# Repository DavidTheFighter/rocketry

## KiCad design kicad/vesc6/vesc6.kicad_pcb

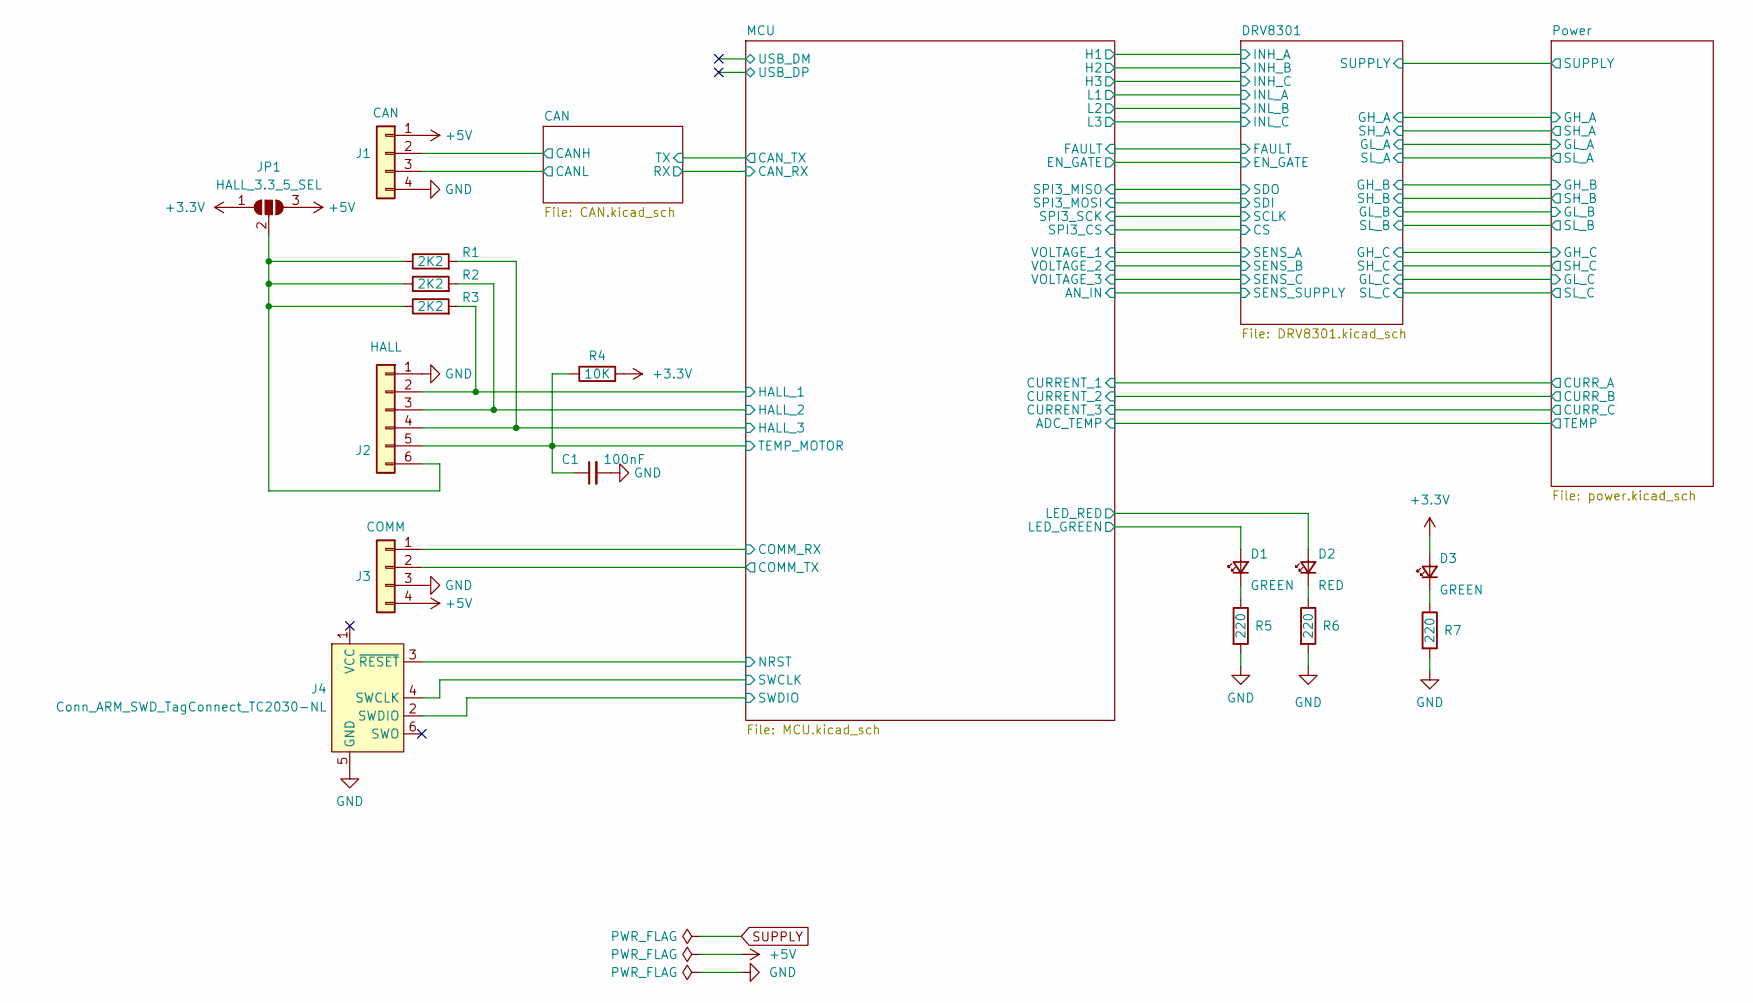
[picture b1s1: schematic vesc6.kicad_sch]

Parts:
C1: 100nF; C_0402_1005Metric; LCSC C307331
D1, D3: GREEN; C_0603_1608Metric; LCSC C72043
D2: RED; C_0603_1608Metric; LCSC C2286
J1: CAN; JST_PH_B4B-PH-K_1x04_P2.00mm_Vertical
J2: HALL; JST_PH_B6B-PH-K_1x06_P2.00mm_Vertical
J3: COMM; JST_PH_B4B-PH-K_1x04_P2.00mm_Vertical
J4: Conn_ARM_SWD_TagConnect_TC2030-NL; Tag-Connect_TC2030-IDC-NL_2x03_P1.27mm_Vertical
JP1: HALL_3.3_5_SEL; SolderJumper-3_P2.0mm_Open_TrianglePad1.0x1.5mm
R1, R2, R3: 2K2; C_0402_1005Metric; LCSC C25879
R4: 10K; R_0402_1005Metric; LCSC C25744
R5, R6, R7: 220; R_0402_1005Metric; LCSC C25091

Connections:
+3.3V: D3.2 (A), JP1.1 (A), R4.2; also elsewhere on the board
+5V: J1.1, J3.4, JP1.3 (B); also elsewhere on the board
/CAN/CANH: J1.2; also elsewhere on the board
/CAN/CANL: J1.3; also elsewhere on the board
/MCU/COMM_RX: J3.1; also elsewhere on the board
/MCU/COMM_TX: J3.2; also elsewhere on the board
/MCU/HALL_1: J2.2, R3.2; also elsewhere on the board
/MCU/HALL_2: J2.3, R2.2; also elsewhere on the board
/MCU/HALL_3: J2.4, R1.2; also elsewhere on the board
/MCU/LED_GREEN: D1.2 (A); also elsewhere on the board
/MCU/LED_RED: D2.2 (A); also elsewhere on the board
/MCU/NRST: J4.3 (~RESET); also elsewhere on the board
/MCU/SWCLK: J4.4 (SWCLK); also elsewhere on the board
/MCU/SWDIO: J4.2 (SWDIO); also elsewhere on the board
/MCU/TEMP_MOTOR: C1.1, J2.5, R4.1; also elsewhere on the board
GND: C1.2, J1.4, J2.1, J3.3, J4.5 (GND), R5.2, R6.2, R7.2; also elsewhere on the board
unnamed: D1.1 (K), R5.1
unnamed: D2.1 (K), R6.1
unnamed: D3.1 (K), R7.1
unnamed: J2.6, JP1.2 (C), R1.1, R2.1, R3.1

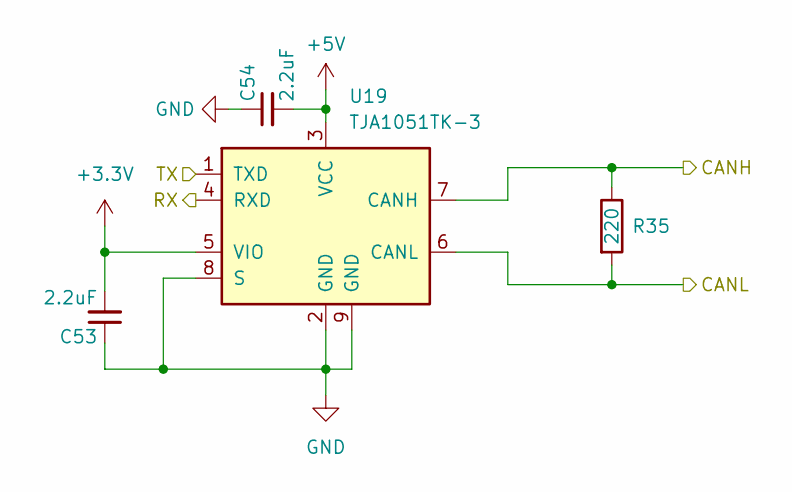
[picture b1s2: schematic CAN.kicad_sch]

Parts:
C53, C54: 2.2uF; R_0603_1608Metric; LCSC C23630
R35: 220; R_0402_1005Metric; LCSC C25091
U19: TJA1051TK-3; DFN-8-1EP_3x3mm_P0.65mm_EP1.55x2.4mm; LCSC C124020

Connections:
+3.3V: C53.2, U19.5 (VIO); also elsewhere on the board
+5V: C54.2, U19.3 (VCC); also elsewhere on the board
/CAN/CANH: R35.1, U19.7 (CANH); also elsewhere on the board
/CAN/CANL: R35.2, U19.6 (CANL); also elsewhere on the board
/CAN/RX: U19.4 (RXD); also elsewhere on the board
/CAN/TX: U19.1 (TXD); also elsewhere on the board
GND: C53.1, C54.1, U19.2 (GND), U19.8 (S), U19.9 (GND); also elsewhere on the board

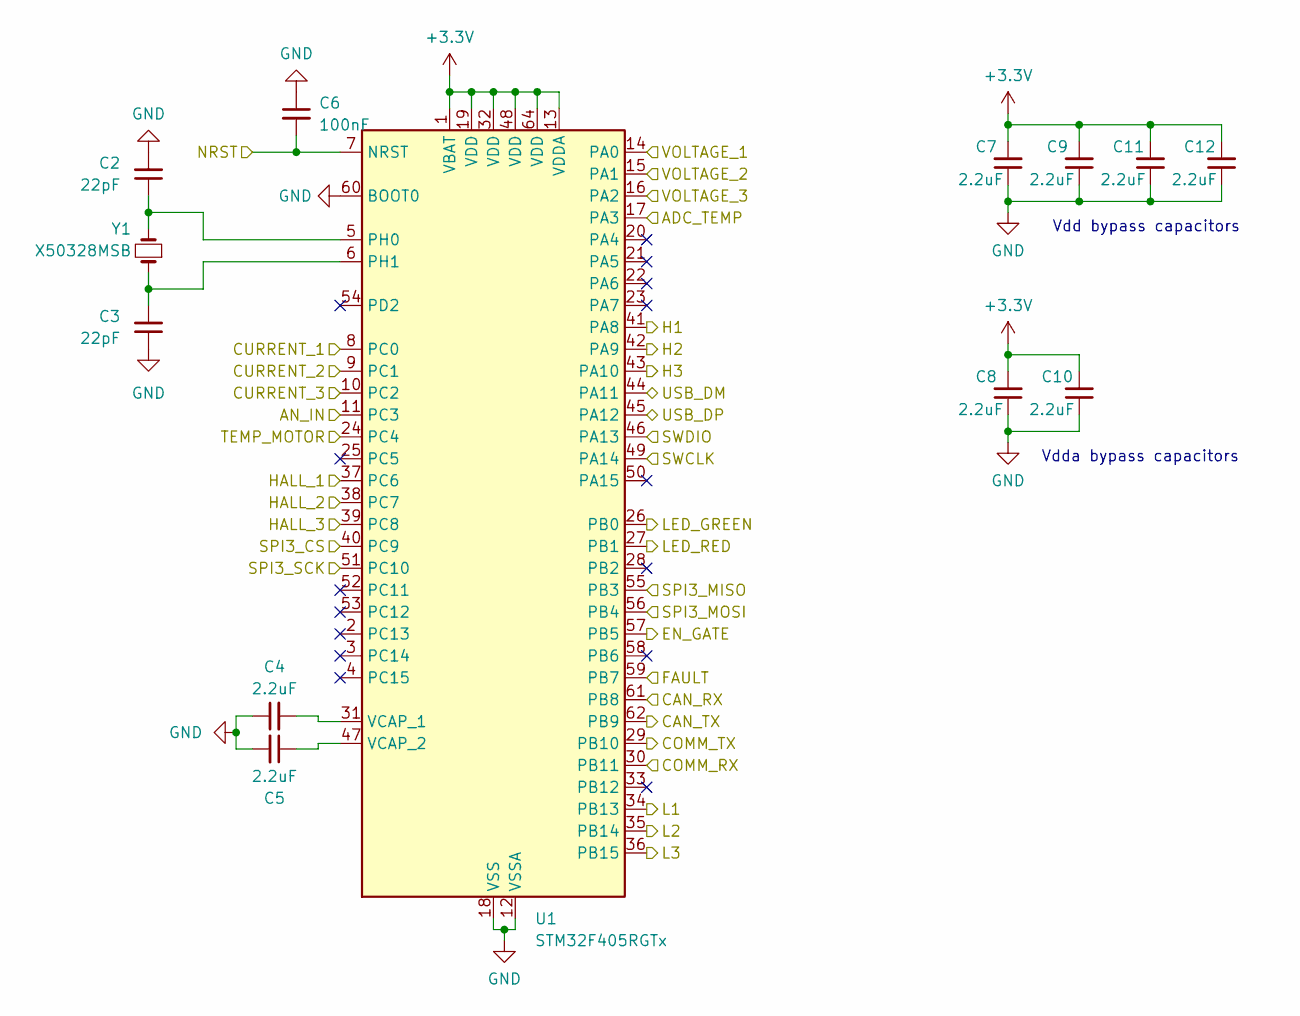
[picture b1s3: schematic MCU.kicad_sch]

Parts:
C2, C3: 22pF; C_0402_1005Metric; LCSC C1555
C4, C5, C7, C8, C9, C10, C11, C12: 2.2uF; C_0603_1608Metric; LCSC C23630
C6: 100nF; C_0504_1310Metric; LCSC C307331
U1: STM32F405RGTx; LQFP-64_10x10mm_P0.5mm; LCSC C15742
Y1: X50328MSB; Crystal_SMD_5032-2Pin_5.0x3.2mm; LCSC C115962

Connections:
+3.3V: C7.2, C8.2, C9.2, C10.2, C11.2, C12.2, U1.1 (VBAT), U1.13 (VDDA), U1.19 (VDD), U1.32 (VDD), U1.48 (VDD), U1.64 (VDD); also elsewhere on the board
/CAN/RX: U1.61 (PB8); also elsewhere on the board
/CAN/TX: U1.62 (PB9); also elsewhere on the board
/DRV8301/CS: U1.40 (PC9); also elsewhere on the board
/DRV8301/EN_GATE: U1.57 (PB5); also elsewhere on the board
/DRV8301/FAULT: U1.59 (PB7); also elsewhere on the board
/DRV8301/INH_A: U1.41 (PA8); also elsewhere on the board
/DRV8301/INH_B: U1.42 (PA9); also elsewhere on the board
/DRV8301/INH_C: U1.43 (PA10); also elsewhere on the board
/DRV8301/INL_A: U1.34 (PB13); also elsewhere on the board
/DRV8301/INL_B: U1.35 (PB14); also elsewhere on the board
/DRV8301/INL_C: U1.36 (PB15); also elsewhere on the board
/DRV8301/SCLK: U1.51 (PC10); also elsewhere on the board
/DRV8301/SDI: U1.56 (PB4); also elsewhere on the board
/DRV8301/SDO: U1.55 (PB3); also elsewhere on the board
/DRV8301/SENS_A: U1.14 (PA0); also elsewhere on the board
/DRV8301/SENS_B: U1.15 (PA1); also elsewhere on the board
/DRV8301/SENS_C: U1.16 (PA2); also elsewhere on the board
/DRV8301/SENS_SUPPLY: U1.11 (PC3); also elsewhere on the board
/MCU/ADC_TEMP: U1.17 (PA3); also elsewhere on the board
/MCU/COMM_RX: U1.30 (PB11); also elsewhere on the board
/MCU/COMM_TX: U1.29 (PB10); also elsewhere on the board
/MCU/CURRENT_1: U1.8 (PC0); also elsewhere on the board
/MCU/CURRENT_2: U1.9 (PC1); also elsewhere on the board
/MCU/CURRENT_3: U1.10 (PC2); also elsewhere on the board
/MCU/HALL_1: U1.37 (PC6); also elsewhere on the board
/MCU/HALL_2: U1.38 (PC7); also elsewhere on the board
/MCU/HALL_3: U1.39 (PC8); also elsewhere on the board
/MCU/LED_GREEN: U1.26 (PB0); also elsewhere on the board
/MCU/LED_RED: U1.27 (PB1); also elsewhere on the board
/MCU/NRST: C6.2, U1.7 (NRST); also elsewhere on the board
/MCU/SWCLK: U1.49 (PA14); also elsewhere on the board
/MCU/SWDIO: U1.46 (PA13); also elsewhere on the board
/MCU/TEMP_MOTOR: U1.24 (PC4); also elsewhere on the board
/MCU/USB_DM: U1.44 (PA11)
/MCU/USB_DP: U1.45 (PA12)
GND: C2.2, C3.1, C4.1, C5.2, C6.1, C7.1, C8.1, C9.1, C10.1, C11.1, C12.1, U1.12 (VSSA), U1.18 (VSS), U1.60 (BOOT0), U1.63 (VSS); also elsewhere on the board
unnamed: C2.1, U1.5 (PH0), Y1.2
unnamed: C3.2, U1.6 (PH1), Y1.1
unnamed: C4.2, U1.31 (VCAP_1)
unnamed: C5.1, U1.47 (VCAP_2)

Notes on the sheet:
Vdda bypass capacitors
Vdd bypass capacitors

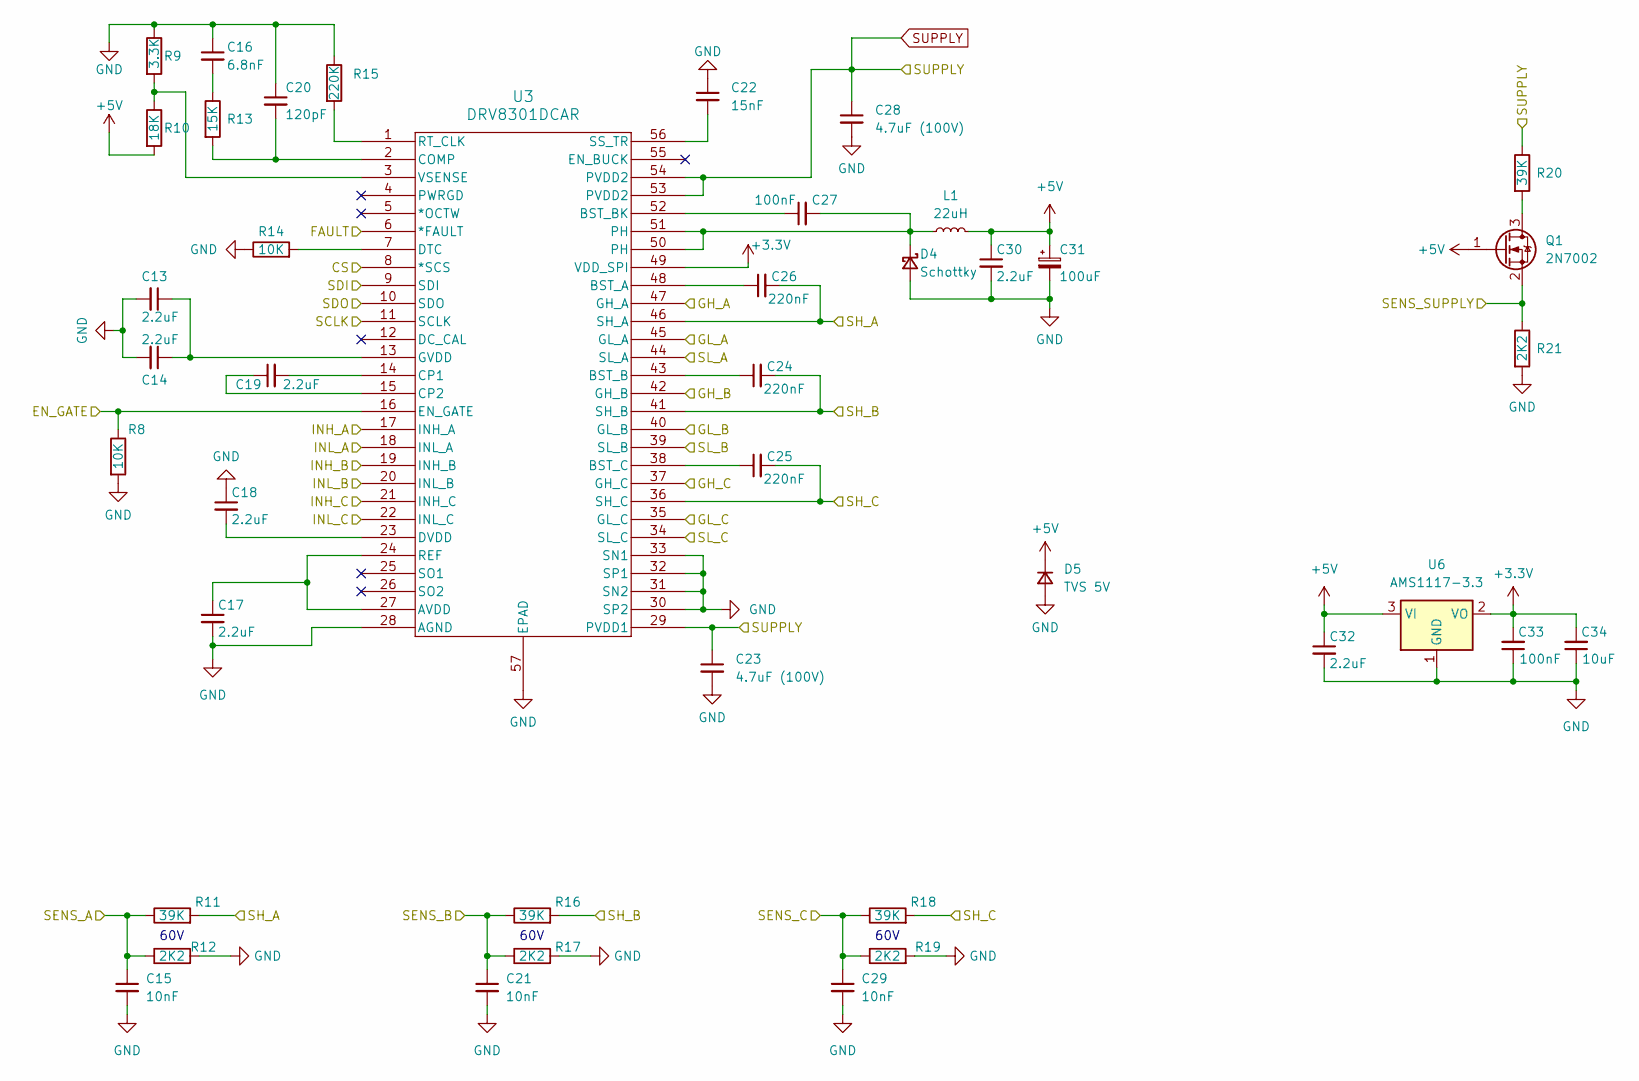
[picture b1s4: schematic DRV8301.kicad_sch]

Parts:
C13, C14, C17, C18, C19, C30, C32: 2.2uF; R_0603_1608Metric; LCSC C23630
C15, C21, C29: 10nF; C_0402_1005Metric; LCSC C15195
C16: 6.8nF; C_0603_1608Metric; LCSC C1631
C20: 120pF; C_0603_1608Metric; LCSC C599667
C22: 15nF; R_0402_1005Metric; LCSC C114405
C23, C28: 4.7uF (100V); R_1210_3225Metric; LCSC C2979983
C24, C25, C26: 220nF; R_0603_1608Metric; LCSC C21120
C27, C33: 100nF; C_0402_1005Metric; LCSC C307331
C31: 100uF; CP_Radial_D6.3mm_P2.50mm
C34: 10uF; C_0603_1608Metric; LCSC C96446
D4: Schottky; D_SMA; LCSC C8678
D5: TVS 5V; D_SOD-923; LCSC C96512
L1: 22uH; L_Bourns_SRP7028A_7.3x6.6mm; LCSC C497873
Q1: 2N7002; SOT-23; LCSC C8545
R8, R14: 10K; R_0402_1005Metric; LCSC C25744
R9: 3.3K; R_0402_1005Metric; LCSC C25890
R10: 18K; R_0603_1608Metric; LCSC C25810
R11, R16, R18, R20: 39K; C_0603_1608Metric; LCSC C23153
R12, R17, R19, R21: 2K2; C_0603_1608Metric; LCSC C4190
R13: 15K; R_0402_1005Metric; LCSC C25756
R15: 220K; R_0603_1608Metric; LCSC C22961
U3: DRV8301DCAR; HTSSOP-56-1EP_6.1x14mm_P0.5mm_EP3.61x6.35mm; LCSC C98969
U6: AMS1117-3.3; SOT-223-3_TabPin2; LCSC C6186

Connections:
+3.3V: C33.2, C34.2, U3.49 (VDD_SPI), U6.2 (VO); also elsewhere on the board
+5V: C30.1, C31.1, C32.1, D5.1 (K), L1.2, Q1.1 (G), R10.2, U6.3 (VI); also elsewhere on the board
/DRV8301/CS: U3.8 (*SCS); also elsewhere on the board
/DRV8301/EN_GATE: R8.1, U3.16 (EN_GATE); also elsewhere on the board
/DRV8301/FAULT: U3.6 (*FAULT); also elsewhere on the board
/DRV8301/GH_A: U3.47 (GH_A); also elsewhere on the board
/DRV8301/GH_B: U3.42 (GH_B); also elsewhere on the board
/DRV8301/GH_C: U3.37 (GH_C); also elsewhere on the board
/DRV8301/GL_A: U3.45 (GL_A); also elsewhere on the board
/DRV8301/GL_B: U3.40 (GL_B); also elsewhere on the board
/DRV8301/GL_C: U3.35 (GL_C); also elsewhere on the board
/DRV8301/INH_A: U3.17 (INH_A); also elsewhere on the board
/DRV8301/INH_B: U3.19 (INH_B); also elsewhere on the board
/DRV8301/INH_C: U3.21 (INH_C); also elsewhere on the board
/DRV8301/INL_A: U3.18 (INL_A); also elsewhere on the board
/DRV8301/INL_B: U3.20 (INL_B); also elsewhere on the board
/DRV8301/INL_C: U3.22 (INL_C); also elsewhere on the board
/DRV8301/SCLK: U3.11 (SCLK); also elsewhere on the board
/DRV8301/SDI: U3.9 (SDI); also elsewhere on the board
/DRV8301/SDO: U3.10 (SDO); also elsewhere on the board
/DRV8301/SENS_A: C15.1, R11.1, R12.1; also elsewhere on the board
/DRV8301/SENS_B: C21.1, R16.1, R17.1; also elsewhere on the board
/DRV8301/SENS_C: C29.1, R18.1, R19.1; also elsewhere on the board
/DRV8301/SENS_SUPPLY: Q1.2 (S), R21.1; also elsewhere on the board
/DRV8301/SH_A: C26.2, R11.2, U3.46 (SH_A); also elsewhere on the board
/DRV8301/SH_B: C24.2, R16.2, U3.41 (SH_B); also elsewhere on the board
/DRV8301/SH_C: C25.2, R18.2, U3.36 (SH_C); also elsewhere on the board
GND: C13.2, C14.2, C15.2, C16.1, C17.2, C18.1, C20.1, C21.2, C22.1, C23.2, C28.2, C29.2, C30.2, C31.2, C32.2, C33.1, C34.1, D4.2 (A), D5.2 (A), R8.2, R9.1, R12.2, R14.1, R15.1, R17.2, R19.2, R21.2, U3.28 (AGND), U3.30 (SP2), U3.31 (SN2), U3.32 (SP1), U3.33 (SN1), U3.34 (SL_C), U3.39 (SL_B), U3.44 (SL_A), U3.57 (EPAD), U6.1 (GND); also elsewhere on the board
unnamed: C16.2, R13.1
unnamed: C27.2, D4.1 (K), L1.1, U3.50 (PH), U3.51 (PH)
unnamed: Q1.3 (D), R20.2
unnamed: C17.1, U3.24 (REF), U3.27 (AVDD)
unnamed: C26.1, U3.48 (BST_A)
unnamed: C24.1, U3.43 (BST_B)
unnamed: C27.1, U3.52 (BST_BK)
unnamed: C25.1, U3.38 (BST_C)
unnamed: C20.2, R13.2, U3.2 (COMP)
unnamed: C19.2, U3.14 (CP1)
unnamed: C19.1, U3.15 (CP2)
unnamed: R14.2, U3.7 (DTC)
unnamed: C18.2, U3.23 (DVDD)
unnamed: C13.1, C14.1, U3.13 (GVDD)
unnamed: R15.2, U3.1 (RT_CLK)
unnamed: C22.2, U3.56 (SS_TR)
unnamed: R9.2, R10.1, U3.3 (VSENSE)
SUPPLY: C23.1, C28.1, R20.1, U3.29 (PVDD1), U3.53 (PVDD2), U3.54 (PVDD2); also elsewhere on the board

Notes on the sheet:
60V

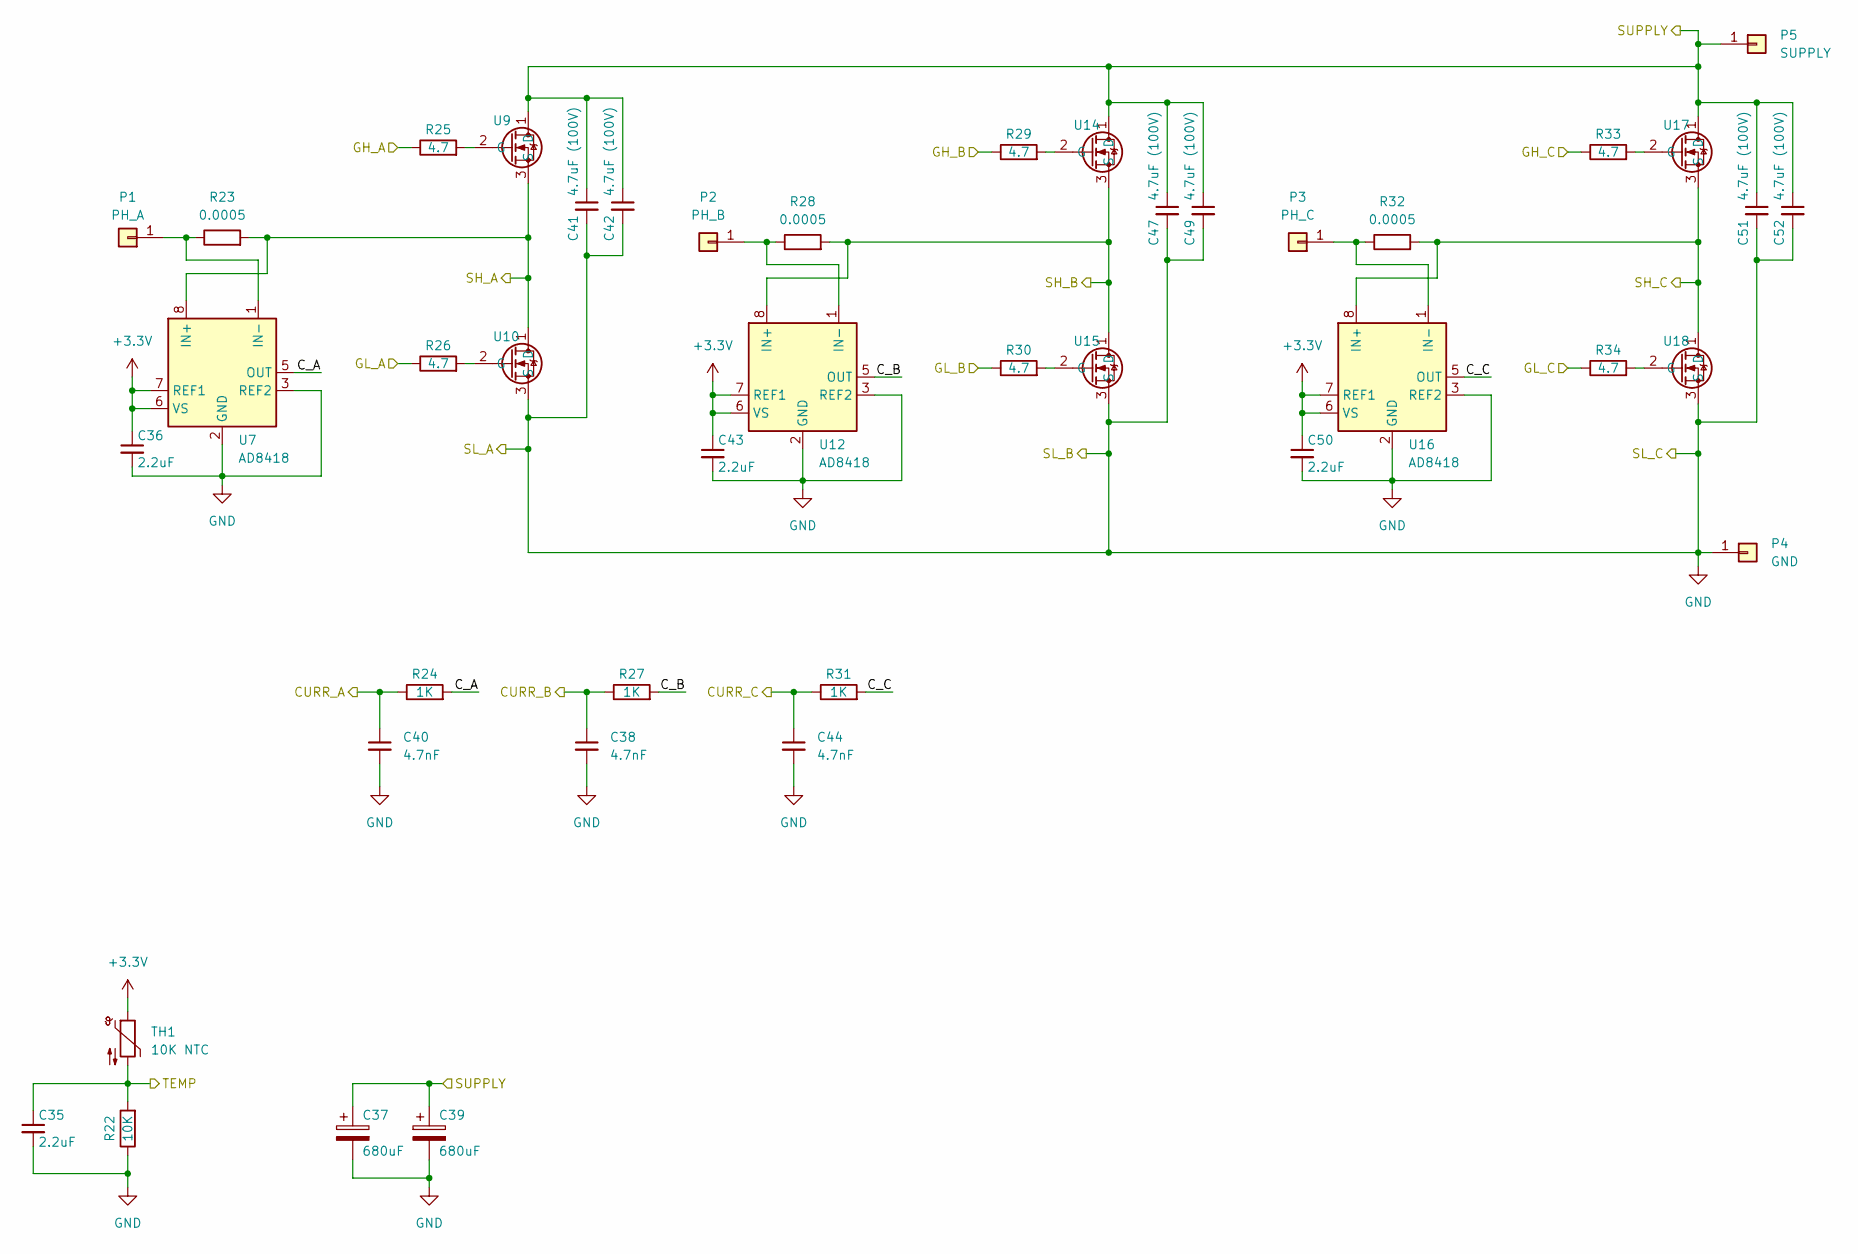
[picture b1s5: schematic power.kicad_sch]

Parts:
C35, C36, C43, C50: 2.2uF; R_0402_1005Metric; LCSC C12530
C37, C39: 680uF; CP_Radial_D18.0mm_P7.50mm
C38, C40, C44: 4.7nF; C_0402_1005Metric; LCSC C1538
C41, C42, C47, C49, C51, C52: 4.7uF (100V); R_1210_3225Metric; LCSC C2979983
P1: PH_A; Pad_10mm
P2: PH_B; Pad_10mm
P3: PH_C; Pad_10mm
P4: GND; Pad_10mm
P5: SUPPLY; Pad_10mm
R22: 10K; R_0402_1005Metric; LCSC C25744
R23, R28, R32: 0.0005; ASR-M-7-0.5F; LCSC C469444
R24, R27, R31: 1K; R_0402_1005Metric; LCSC C11702
R25, R26, R29, R30, R33, R34: 4.7; R_0805_2012Metric; LCSC C17675
TH1: 10K NTC; R_0603_1608Metric; LCSC C524451
U7, U12, U16: AD8418; SOIC-8-N7_3.9x4.9mm_P1.27mm; LCSC C462197
U9, U10, U14, U15, U17, U18: DirectFET_L8; LCSC C520641

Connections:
+3.3V: C36.1, C43.1, C50.1, TH1.1, U7.6 (VS), U7.7 (REF1), U12.6 (VS), U12.7 (REF1), U16.6 (VS), U16.7 (REF1); also elsewhere on the board
/DRV8301/GH_A: R25.1; also elsewhere on the board
/DRV8301/GH_B: R29.1; also elsewhere on the board
/DRV8301/GH_C: R33.1; also elsewhere on the board
/DRV8301/GL_A: R26.1; also elsewhere on the board
/DRV8301/GL_B: R30.1; also elsewhere on the board
/DRV8301/GL_C: R34.1; also elsewhere on the board
/DRV8301/SH_A: R23.2, U7.8 (IN+), U9.3 (S), U10.1 (D); also elsewhere on the board
/DRV8301/SH_B: R28.2, U12.8 (IN+), U14.3 (S), U15.1 (D); also elsewhere on the board
/DRV8301/SH_C: R32.2, U16.8 (IN+), U17.3 (S), U18.1 (D); also elsewhere on the board
/MCU/ADC_TEMP: C35.1, R22.2, TH1.2; also elsewhere on the board
/MCU/CURRENT_1: C40.1, R24.1; also elsewhere on the board
/MCU/CURRENT_2: C38.1, R27.1; also elsewhere on the board
/MCU/CURRENT_3: C44.1, R31.1; also elsewhere on the board
/Power/C_A: R24.2, U7.5 (OUT)
/Power/C_B: R27.2, U12.5 (OUT)
/Power/C_C: R31.2, U16.5 (OUT)
GND: C35.2, C36.2, C37.2, C38.2, C39.2, C40.2, C41.2, C42.2, C43.2, C44.2, C47.2, C49.2, C50.2, C51.2, C52.2, P4.1, R22.1, U7.2 (GND), U7.3 (REF2), U10.3 (S), U12.2 (GND), U12.3 (REF2), U15.3 (S), U16.2 (GND), U16.3 (REF2), U18.3 (S); also elsewhere on the board
unnamed: P1.1, R23.1, U7.1 (IN-)
unnamed: P2.1, R28.1, U12.1 (IN-)
unnamed: P3.1, R32.1, U16.1 (IN-)
unnamed: R25.2, U9.2 (G)
unnamed: R26.2, U10.2 (G)
unnamed: R29.2, U14.2 (G)
unnamed: R30.2, U15.2 (G)
unnamed: R33.2, U17.2 (G)
unnamed: R34.2, U18.2 (G)
SUPPLY: C37.1, C39.1, C41.1, C42.1, C47.1, C49.1, C51.1, C52.1, P5.1, U9.1 (D), U14.1 (D), U17.1 (D); also elsewhere on the board

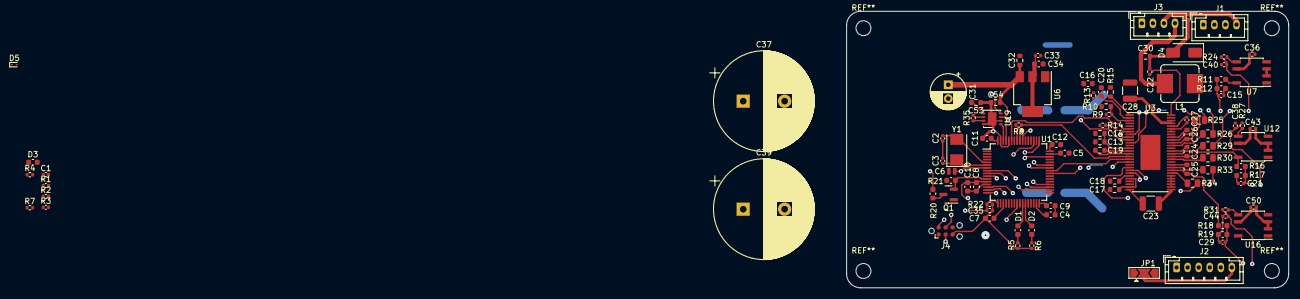
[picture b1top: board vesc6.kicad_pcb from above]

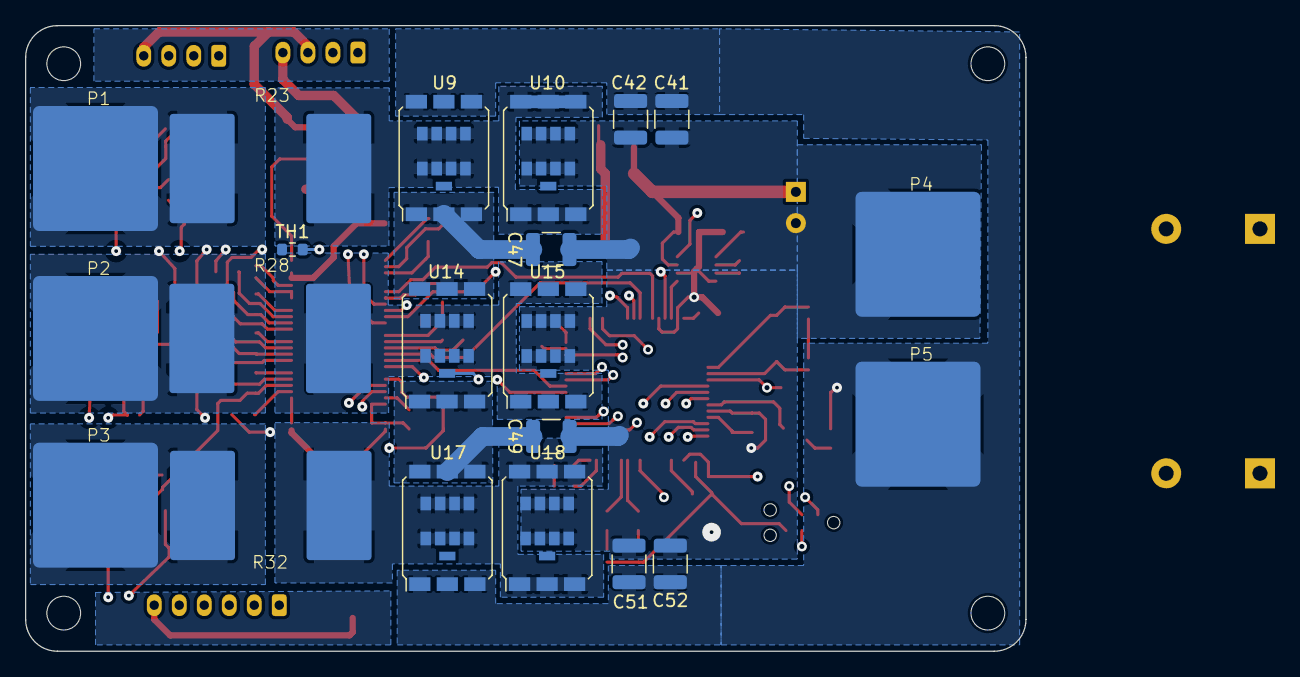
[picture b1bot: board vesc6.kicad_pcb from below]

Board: 4 copper layers, 80.0 x 50.0 mm, 118 parts (21 on the bottom side), 85 nets.

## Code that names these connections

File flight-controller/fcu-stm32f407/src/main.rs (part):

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    use shared::comms_hal::{NetworkAddress, Packet};
    use stm32f4::stm32f407::{I2C1, DMA2, ADC1};
    use stm32f4xx_hal::{
        gpio::{self, Input, Output, PC3, PC14, PC15, PE4, PE5, PE8, PE9, Edge, Pin, Alternate, PinState},
        prelude::*,
        spi,
        pac::{SPI1, USART2, UART4},
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
    #[local]
    struct Local {
        blue_led: PC14<Output>,
        bmi088_accel: Bmi088Accelerometer<SharedI2C1Type>,
        bmi088_gyro: Bmi088Gyroscope<SharedI2C1Type>,
        ms5611: ms5611_rs::Ms5611<SharedI2C1Type>,
        bmm150: bmm150::Bmm150,
        accel_int_pin: PE8<Input>,
        gyro_int_pin: PE9<Input>,
        mag_int_pin: PC3<Input>,
        // usart2: Serial<USART2, (Pin<'D', 5, Alternate<7>>, Pin<'D', 6, Alternate<7>>)>,
        uart4: Serial<UART4, (Pin<'C', 10, Alternate<8>>, Pin<'C', 11, Alternate<8>>)>,
        adc1_transfer: Transfer<dma::StreamX<DMA2, 0>, 0, Adc<ADC1>, dma::PeripheralToMemory, &'static mut [u16; 8]>,
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
    #[shared]
    struct Shared {
        red_led: PC15<Output>,
        fcu: Fcu<'static>,
        #[lock_free]
        w25x05: w25x05::W25X05<PE4<Output>, PE5<Output>>,
        #[lock_free]
        spi1: LogSpi1,
        cpu_utilization: AtomicU32,
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
        #[task(
            binds = EXTI9_5,
            local = [bmi088_accel, bmi088_gyro, accel_int_pin, gyro_int_pin],
            shared = [fcu],
            priority = 11,
        )]
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        let gpiod = p.GPIOD.split();
        let gpioe = p.GPIOE.split();

        let blue_led = gpioc.pc14.into_push_pull_output();
        let red_led = gpioc.pc15.into_push_pull_output();

        let rcc = p.RCC.constrain();
        let clocks = rcc
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        core.DCB.enable_trace();
        core.DWT.enable_cycle_counter();

        let output1_ctrl = gpioe.pe0.into_push_pull_output_in_state(PinState::Low);
        let output2_ctrl = gpioe.pe1.into_push_pull_output_in_state(PinState::Low);
        let output3_ctrl = gpioe.pe2.into_push_pull_output_in_state(PinState::Low);
        let output4_ctrl = gpioe.pe3.into_push_pull_output_in_state(PinState::Low);

        let output1_cont = gpioa.pa3.into_analog();
        let output2_cont = gpioa.pa4.into_analog();
        let output3_cont = gpioa.pa6.into_analog();
        let output4_cont = gpiob.pb0.into_analog();

        let i2c1_scl = gpiob.pb6.into_alternate_open_drain();
        let i2c1_sda = gpiob.pb7.into_alternate_open_drain();

        let spi1_sck = gpioa.pa5.into_alternate();
        let spi1_miso = gpiob.pb4.into_alternate();
        let spi1_mosi = gpiob.pb5.into_alternate();

        let log_flash_csn = gpioe.pe4.into_push_pull_output_in_state(PinState::High);
        let log_flash_hold = gpioe.pe5.into_push_pull_output_in_state(PinState::High);

        let usart2_tx = gpiod.pd5.into_alternate();
        let usart2_rx = gpiod.pd6.into_alternate();

        let uart4_tx = gpioc.pc10.into_alternate();
        let uart4_rx = gpioc.pc11.into_alternate();

        let dma2 = StreamsTuple::new(p.DMA2);

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        );

        let tim2_pwm = p.TIM2.pwm_hz((
            gpioa.pa15.into_alternate(),
            gpiob.pb3.into_alternate(),
        ), 50.Hz(), &clocks);

        let (mut ch1, mut ch2) = tim2_pwm.split();
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        ).unwrap().with_u8_data();

        let eth_pins = stm32_eth::EthPins {
            ref_clk: gpioa.pa1,
            crs: gpioa.pa7,
            tx_en: gpiob.pb11,
            tx_d0: gpiob.pb12,
            tx_d1: gpiob.pb13,
            rx_d0: gpioc.pc4,
            rx_d1: gpioc.pc5,
        };

        let ethernet_parts = stm32_eth::PartsIn {
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        bmi088_gyro.set_bandwidth(GyroBandwidth::Data100Filter12).unwrap();
        bmi088_gyro.configure_int3_pin(Bmi088PinBehavior::PushPull, true, true).unwrap();

        let mut accel_int_pin = gpioe.pe8.into_pull_down_input();
        accel_int_pin.make_interrupt_source(&mut syscfg);
        accel_int_pin.enable_interrupt(&mut p.EXTI);
        accel_int_pin.trigger_on_edge(&mut p.EXTI, Edge::Rising);

        let mut gyro_int_pin = gpioe.pe9.into_pull_down_input();
        gyro_int_pin.make_interrupt_source(&mut syscfg);
        gyro_int_pin.enable_interrupt(&mut p.EXTI);
        gyro_int_pin.trigger_on_edge(&mut p.EXTI, Edge::Rising);

        let mut mag_int_pin = gpioc.pc3.into_pull_down_input();
        mag_int_pin.make_interrupt_source(&mut syscfg);
        mag_int_pin.enable_interrupt(&mut p.EXTI);
        mag_int_pin.trigger_on_edge(&mut p.EXTI, Edge::Rising);
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                bmi088_gyro,
                ms5611,
                bmm150,
                accel_int_pin,
                gyro_int_pin,
                mag_int_pin,
                uart4,
                adc1_transfer,
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fn red_led_panic(_: &PanicInfo) -> ! {
    let dp = unsafe { pac::Peripherals::steal() };
    let gpioc = dp.GPIOC.split();
    let mut red_led = gpioc.pc15.into_push_pull_output();

    loop {
        red_led.set_low();
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
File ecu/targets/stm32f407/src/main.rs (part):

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            Adc, Temperature,
        },
        dma::{config::DmaConfig, StreamsTuple, Transfer},
        gpio::{Output, PE5},
        prelude::*,
    };
    use systick_monotonic::Systick;
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
    #[local]
    struct Local {
        blue_led: PE5<Output>,
        adc: ADCStorage,
        dwt: DWT,
        ecu_module: engine_controller::Ecu<'static, Stm32F407EcuDriver>,
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        let gpioe = p.GPIOE.split();
        let gpiof = p.GPIOF.split();

        let blue_led = gpioe.pe5.into_push_pull_output();
        let spark_ctrl = gpioe.pe9.into_alternate().internal_pull_down(true);
        let sv1_ctrl = gpioa.pa12.into_push_pull_output();
        let sv2_ctrl = gpioa.pa11.into_push_pull_output();
        let sv3_ctrl = gpioa.pa10.into_push_pull_output();
        let sv4_ctrl = gpioa.pa9.into_push_pull_output();
        let adc_in3 = gpioa.pa3.into_analog();
        let adc_in4 = gpioa.pa4.into_analog();
        let adc_in5 = gpioa.pa5.into_analog();
        let adc_in6 = gpioa.pa6.into_analog();
        let adc_in7 = gpiof.pf9.into_analog();
        // let adc_in8 = gpiof.pf10.into_analog();

        let mut spark_ctrl = p.TIM1.pwm_hz(spark_ctrl, 400.Hz(), &clocks).split();
        spark_ctrl.disable();
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            Transfer::init_peripheral_to_memory(dma2.1, adc3, adc3_buffer1, None, dma_config);

        let eth_pins = EthPins {
            ref_clk: gpioa.pa1,
            crs: gpioa.pa7,
            tx_en: gpiob.pb11,
            tx_d0: gpiob.pb12,
            tx_d1: gpiob.pb13,
            rx_d0: gpioc.pc4,
            rx_d1: gpioc.pc5,
        };
        let (eth_dma, _eth_mac) = stm32_eth::new(
            p.ETHERNET_MAC,
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fn panic(_info: &PanicInfo) -> ! {
    let dp = unsafe { pac::Peripherals::steal() };
    let gpioe = dp.GPIOE.split();
    let mut led = gpioe.pe5.into_push_pull_output();

    loop {
        led.set_low();
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
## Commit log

2022-11-27 Transferred igni ECU KiCAD files to new project
2022-12-13 Big initial push, oops
2022-12-17 Initial vue.js project
2022-12-18 Got realtime line graph working w/ fake data
2022-12-19 Added terminal & hardware/software states to UI
2022-12-19 Fixed/changed UI to work on smaller screens
2022-12-21 mission-ctrl progress on commands & comms w/ ECU
2022-12-21 Fixed bugs and some function for basic igniter
2022-12-22 Added data logging, sensor config, and more commands
2022-12-22 Refactored FSMs
2022-12-22 Removed firmware binary files from git
2022-12-23 Added testspark command
2022-12-23 Fixed recording file name on Windows
2022-12-24 cargo fmt + ADC bug fix + other small changes
2022-12-24 Added a CPU utilization metric
2022-12-24 Playing around with a new state machine model
2022-12-26 Updated sensor config to work with my hardware
2022-12-28 Added Depressurized state to fuel tank FSM
2022-12-29 Added script to plot recorded firing data
2022-12-30 Changes during first test runs
2023-01-06 Added some design scripts using RocketCEA
2023-01-06 Added more config, calibrations, and state logic
2023-01-06 Fixed CPU usage issue caused by compiler reordering
2023-01-17 Engine CEA work
2023-01-17 Progress on the abstracted engine controller
2023-01-17 Disabled the spark plug in the firing state
2023-01-26 Dump so I can work from my laptop
2023-02-02 Lots o changes, pushing to work on my laptop
2023-03-11 Changes dump again. Oops :)
2023-03-22 Rewrote mission-ctrl-server
2023-03-24 Closer to being finished on mission-ctrl rewrite
2023-03-24 Ecu abstraction is now working
2023-04-14 Omg so many changes
2023-04-20 Routing work on FCU v0.2
2023-04-20 Added python reqs
2023-04-20 Updated KiCad to be switchable between computers
2023-04-26 FCU PCB Work
2023-05-12 mission-control-ui rocket page + FCU simulation
2023-05-30 I "was" getting better at comitting more often...
2023-07-14 Oh lordy that's a lot of changes
2023-07-24 Lots of dev stats work
2023-07-26 Starting changes for cameras
2023-07-26 Added a streamish project
2023-07-26 Maybe fixed github workflows
2023-07-27 Cross compiling streamish
2023-07-28 More attempts
2023-08-01 Address management in mission-ctrl-server
2023-08-03 Streaming progress
2023-08-03 Streaming and transcoding work!
2023-08-05 More streaming progress (pt x/n)
2023-08-07 Streamish workscargo run --release!
2023-08-07 WIP Upload
2023-08-08 Streamish can do dynamics commands now
2023-08-10 Dunno
2023-08-10 Running out of creative names
2023-08-11 Network manager
2023-08-12 Fixed unit test
2023-08-14 Comms manager is working!
2023-08-15 Fix streamish
2023-08-15 Fully integrated comms manager
2023-08-21 Pump design stuff
2023-09-11 General work
2023-10-14 Comms changes + shared code
2023-10-14 Mission control updates
2023-10-16 Barometer + calibration
2023-10-23 Sensor work + calibrating + zeroing
2023-10-28 Reintegrated SIL
2023-10-28 Merged hal into shared
2023-10-30 Restructuring
2023-11-06 Lots of new testing!
2023-11-06 Updates + CI changes
2023-11-07 Fleshed out states a bit
2023-11-11 Solid motor ignition control
2023-11-11 Removed old hal/ + added proto alert system
2023-11-14 Bootloader start
2023-11-18 Bootloader progress
2023-11-23 Realtime sim works w/ mission-ctrl-server + cleanup
2023-11-24 Moved state machine trait to shared
2023-11-25 Got bootloader working
2023-11-25 Got bootloader programmer working
2023-11-26 Made bootloader nice to use
2023-11-26 Logging works w/o hardware integration
2023-12-09 Added big-brother comms system
2023-12-10 Got stuff building w/ big brother!
2023-12-12 Got big brother working!
2023-12-18 Big brother sessions + FCU debug page
2023-12-19 Make ethboot-program use big brother
2023-12-23 Added mock networking to BB
2024-01-08 Lots of big brother updates
2024-01-12 Sim network topo + fixed simulation app
2024-01-13 Multiplexed FcuDebugInfo
2024-01-16 Got a basic unscented kalman filter working!
2024-01-20 FCU Sensor logging + sim UI tweaks
2024-01-20 Added basic bitrate measurement
2024-01-21 Refactored ECU project structure
2024-01-23 Updated ECU to 2024 + cargo fmt
2024-02-02 Got ECU updated to 2024
2024-02-05 Support for multiple ECUs-ish + engine CEA
2024-02-07 Added more ecu tests + better sim glue
2024-02-13 Progress on engine
2024-03-07 Crap too many changes
2024-03-08 Added state vector to ECU
2024-03-14 General maintanence
2024-03-16 Some cleanup/comments
2024-03-24 SIL now properly timesteps data + fluid pipes
2024-03-24 Fix igniter abort test
2024-03-28 Better sensor measurements in SIL
2024-03-29 Cleaned up sim sensors
2024-04-01 Got ECU MCU updated
2024-04-03 Sil improvements
2024-04-03 Simulating pumps!
2024-04-04 Added pump tests + cleaned up old tests
2024-04-12 Sim + Engine improvements
2024-04-16 Added basic engine simulation
2024-06-14 That's a lot of changes
2024-07-04 Now using websockets for telemetry webpages
2024-08-07 Got a first pass mission-ctrl interface working
2024-08-07 Changed ECU v0.4 to use more fused outputs
2024-11-30 Better sim configs + ecu v0.4 work
2024-12-18 Lots of sim changes oof
2024-12-24 Cleaned up Cargo.toml's + fixed some UI bugs
2024-12-29 improved self press + tank tests + cargo fmt
2024-12-29 Updated python module structure + fully codified config gen!
2024-12-29 Refactor configs & simulation
2024-12-31 Progress on ECU v0.4
2025-01-17 Merged mission-ctrl-api into simulation
2025-01-17 cargo fmt
